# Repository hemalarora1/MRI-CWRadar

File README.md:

# MRI-CWRadar
Research Project at Stanford Magnetic Resonance Systems Research Laboratory. Summer 2024.

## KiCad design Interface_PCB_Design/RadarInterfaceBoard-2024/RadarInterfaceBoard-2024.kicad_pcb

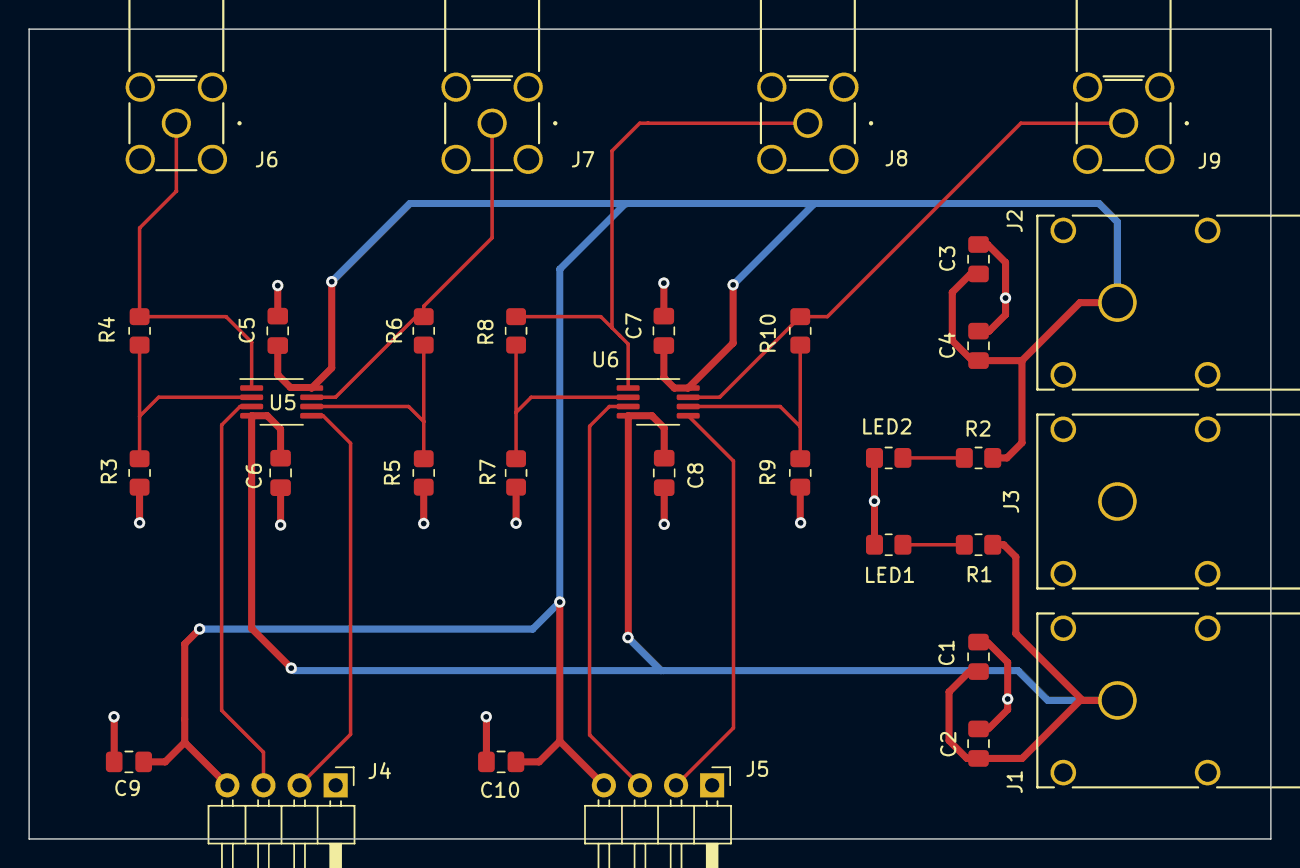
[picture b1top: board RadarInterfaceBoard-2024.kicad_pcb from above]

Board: 2 copper layers, 87.4 x 57.0 mm, 33 parts (0 on the bottom side), 17 nets.

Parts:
C1, C3, C5, C6, C7, C8, C9, C10: 0.1uF; C_0805_2012Metric_Pad1.18x1.45mm_HandSolder
C2, C4: 10uF; C_0805_2012Metric_Pad1.18x1.45mm_HandSolder
J1, J2, J3: 73099-0; CONN_73099-0_POM
J4, J5: Conn_01x04_Pin; PinHeader_1x04_P2.54mm_Horizontal
J6, J7, J8, J9: CONSMA002; COAX4GND_731000115_MOL
LED1, LED2: D; R_0805_2012Metric_Pad1.20x1.40mm_HandSolder
R1, R2: R; R_0805_2012Metric_Pad1.20x1.40mm_HandSolder
R3, R5, R7, R9: 1k; R_0805_2012Metric_Pad1.20x1.40mm_HandSolder
R4, R6, R8, R10: 10k; R_0805_2012Metric_Pad1.20x1.40mm_HandSolder
U5, U6: ADA4807-2ARM; MSOP-8_3x3mm_P0.65mm

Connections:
1I: J4.2, U5.5 (+)
1Q: J4.3, U5.3 (+)
2I: J5.2, U6.5 (+)
2Q: J5.3, U6.3 (+)
/V+: C3.1, C4.1, C5.1, C7.1, C9.1, C10.1, J2.1, J4.4, J5.4, R2.1, U5.8 (V+), U6.8 (V+)
/V-: C1.1, C2.1, C6.1, C8.1, J1.1, R1.2, U5.4 (V-), U6.4 (V-)
GND: C1.2, C2.2, C3.2, C4.2, C5.2, C6.2, C7.2, C8.2, C9.2, C10.2, J3.1, J4.1, J5.1, J6.2 (GND), J6.3 (GND), J6.4 (GND), J6.5 (GND), J7.2 (GND), J7.3 (GND), J7.4 (GND), J7.5 (GND), J8.2 (GND), J8.3 (GND), J8.4 (GND), J8.5 (GND), J9.2 (GND), J9.3 (GND), J9.4 (GND), J9.5 (GND), LED1.2 (A), LED2.1 (K), R3.1, R5.1, R7.1, R9.1
unnamed: LED1.1 (K), R1.1
unnamed: LED2.2 (A), R2.2
unnamed: R3.2, R4.1, U5.2 (-)
unnamed: R5.2, R6.1, U5.6 (-)
unnamed: R7.2, R8.1, U6.2 (-)
unnamed: R9.2, R10.1, U6.6 (-)
SMA1I: J7.1 (SIGNAL), R6.2, U5.7
SMA1Q: J6.1 (SIGNAL), R4.2, U5.1
SMA2I: J9.1 (SIGNAL), R10.2, U6.7
SMA2Q: J8.1 (SIGNAL), R8.2, U6.1

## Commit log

2024-07-10 initial schematic for radar interface board
2024-07-11 schematic iteration 1 complete, some project-specific symbols included
2024-07-11 changed bnc to sma connectors, attempted start at pcb layout
2024-07-12 changed sma connector footprint, added ground pour to pcb layout
2024-07-12 pcb layout iteration complete
2024-07-12 added bypass capacitors for KLC5 radar header pins
2024-07-13 adjusted spacing of sma connectors and slight pcb trace modification
2024-07-24 fixed op-amp gain
2024-07-24 file renaming
2024-07-27 wrote script for signal processing
2024-08-30 run_experiments.py file in full working condition; SSA and ICA processing pipeline complete
2024-08-30 Added poster
2024-08-30 added poster jpeg
2024-09-03 tweaks made to SSA_and_ICA.m post-processing script
2024-11-05 changes made in preparation of ISMRM submission
